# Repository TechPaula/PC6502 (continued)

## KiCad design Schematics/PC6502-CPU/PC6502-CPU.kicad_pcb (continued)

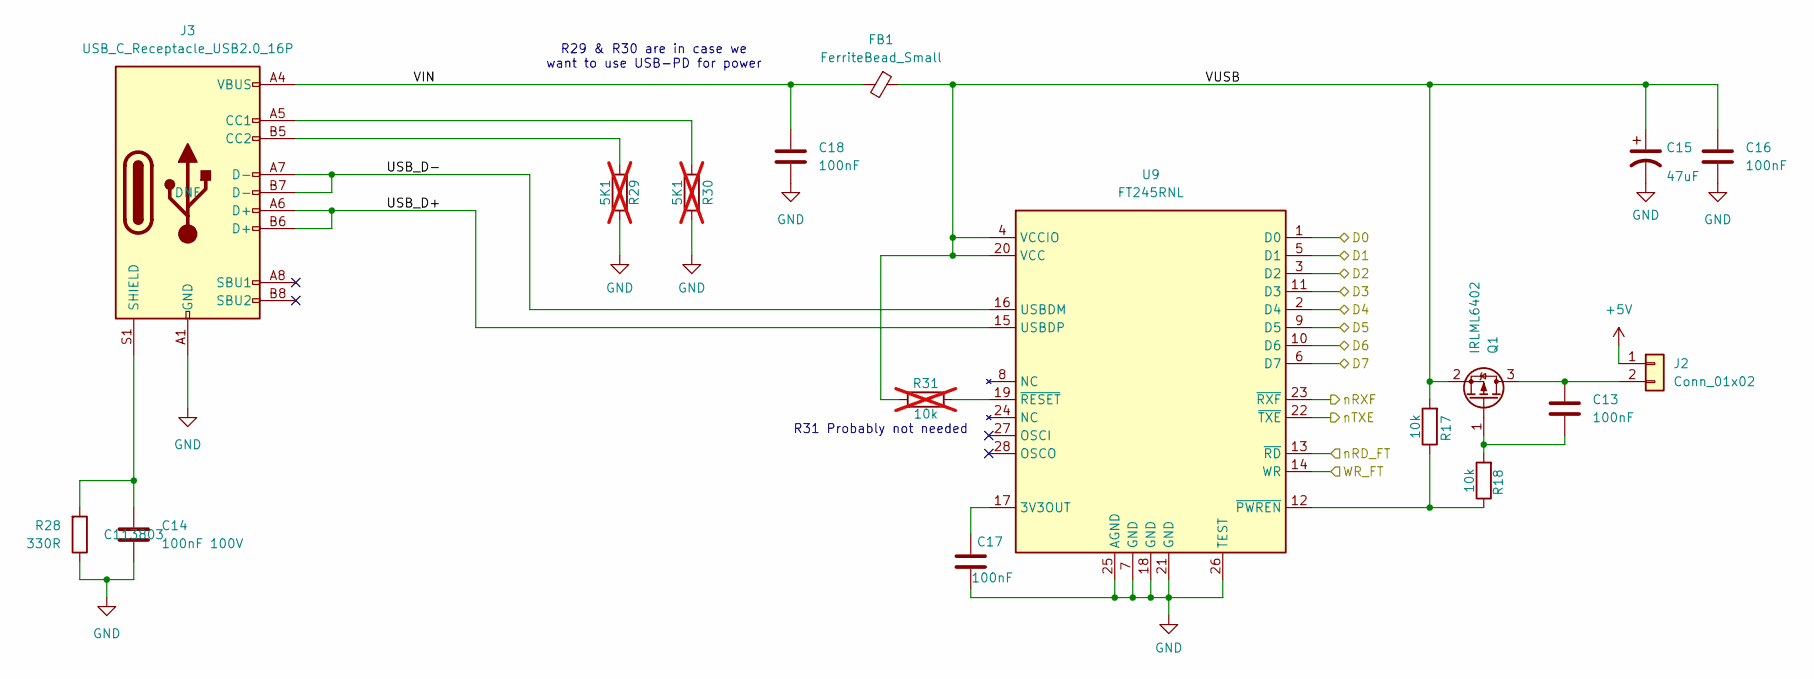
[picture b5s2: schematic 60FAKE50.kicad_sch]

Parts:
C13, C17: 100nF; C_0603_1608Metric_Pad1.08x0.95mm_HandSolder; LCSC C113803
C14: 100nF 100V; C_0603_1608Metric; LCSC C113803
C15: 47uF; C_1206_3216Metric; LCSC C96123
C16, C18: 100nF; C_0805_2012Metric; LCSC C49678
FB1: FerriteBead_Small; L_0805_2012Metric_Pad1.05x1.20mm_HandSolder; LCSC DNF
J2: Conn_01x02; PinHeader_1x02_P2.54mm_Horizontal; LCSC DNF
J3: USB_C_Receptacle_USB2.0_16P; USB_C_Receptacle_HCTL_HC-TYPE-C-16P-01A; LCSC DNF
Q1: IRLML6402; SOT-23; LCSC C2593
R17, R18: 10k; R_0603_1608Metric_Pad0.98x0.95mm_HandSolder; LCSC C25744
R28: 330R; R_0402_1005Metric; LCSC C25104
R29, R30: 5K1; R_0603_1608Metric_Pad0.98x0.95mm_HandSolder; LCSC DNF; not fitted
R31: 10k; R_0603_1608Metric_Pad0.98x0.95mm_HandSolder; LCSC DNF; not fitted
U9: FT245RNL; SSOP-28_5.3x10.2mm_P0.65mm; LCSC C6558294

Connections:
+5V: J2.1; also elsewhere on the board
/60FAKE50/USB_D+: J3.A6 (D+), J3.B6 (D+), U9.15 (USBDP)
/60FAKE50/USB_D-: J3.A7 (D-), J3.B7 (D-), U9.16 (USBDM)
/60FAKE50/VIN: C18.1, FB1.2, J3.A4 (VBUS), J3.A9 (VBUS), J3.B4 (VBUS), J3.B9 (VBUS)
/60FAKE50/VUSB: C15.1, C16.1, FB1.1, Q1.2 (S), R17.2, R31.2, U9.4 (VCCIO), U9.20 (VCC)
/D0: U9.1 (D0); also elsewhere on the board
/D1: U9.5 (D1); also elsewhere on the board
/D2: U9.3 (D2); also elsewhere on the board
/D3: U9.11 (D3); also elsewhere on the board
/D4: U9.2 (D4); also elsewhere on the board
/D5: U9.9 (D5); also elsewhere on the board
/D6: U9.10 (D6); also elsewhere on the board
/D7: U9.6 (D7); also elsewhere on the board
GND: C14.2, C15.2, C16.2, C17.2, C18.2, J3.A1 (GND), J3.A12 (GND), J3.B1 (GND), J3.B12 (GND), R28.1, R29.1, R30.1, U9.7 (GND), U9.18 (GND), U9.21 (GND), U9.25 (AGND), U9.26 (TEST); also elsewhere on the board
unnamed: C13.1, J2.2, Q1.3 (D)
unnamed: J3.A5 (CC1), R30.2
unnamed: J3.B5 (CC2), R29.2
unnamed: C14.1, J3.S1 (SHIELD), R28.2
unnamed: C13.2, Q1.1 (G), R18.2
unnamed: C17.1, U9.17 (3V3OUT)
unnamed: R17.1, R18.1, U9.12 (~PWREN)
unnamed: R31.1, U9.19 (~RESET)
WR_FT: U9.14 (WR); also elsewhere on the board
nRD_FT: U9.13 (~RD); also elsewhere on the board
nRXF: U9.23 (~RXF); also elsewhere on the board
nTXE: U9.22 (~TXE); also elsewhere on the board

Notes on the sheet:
R29 & R30 are in case we want to use USB-PD for power
R31 Probably not needed

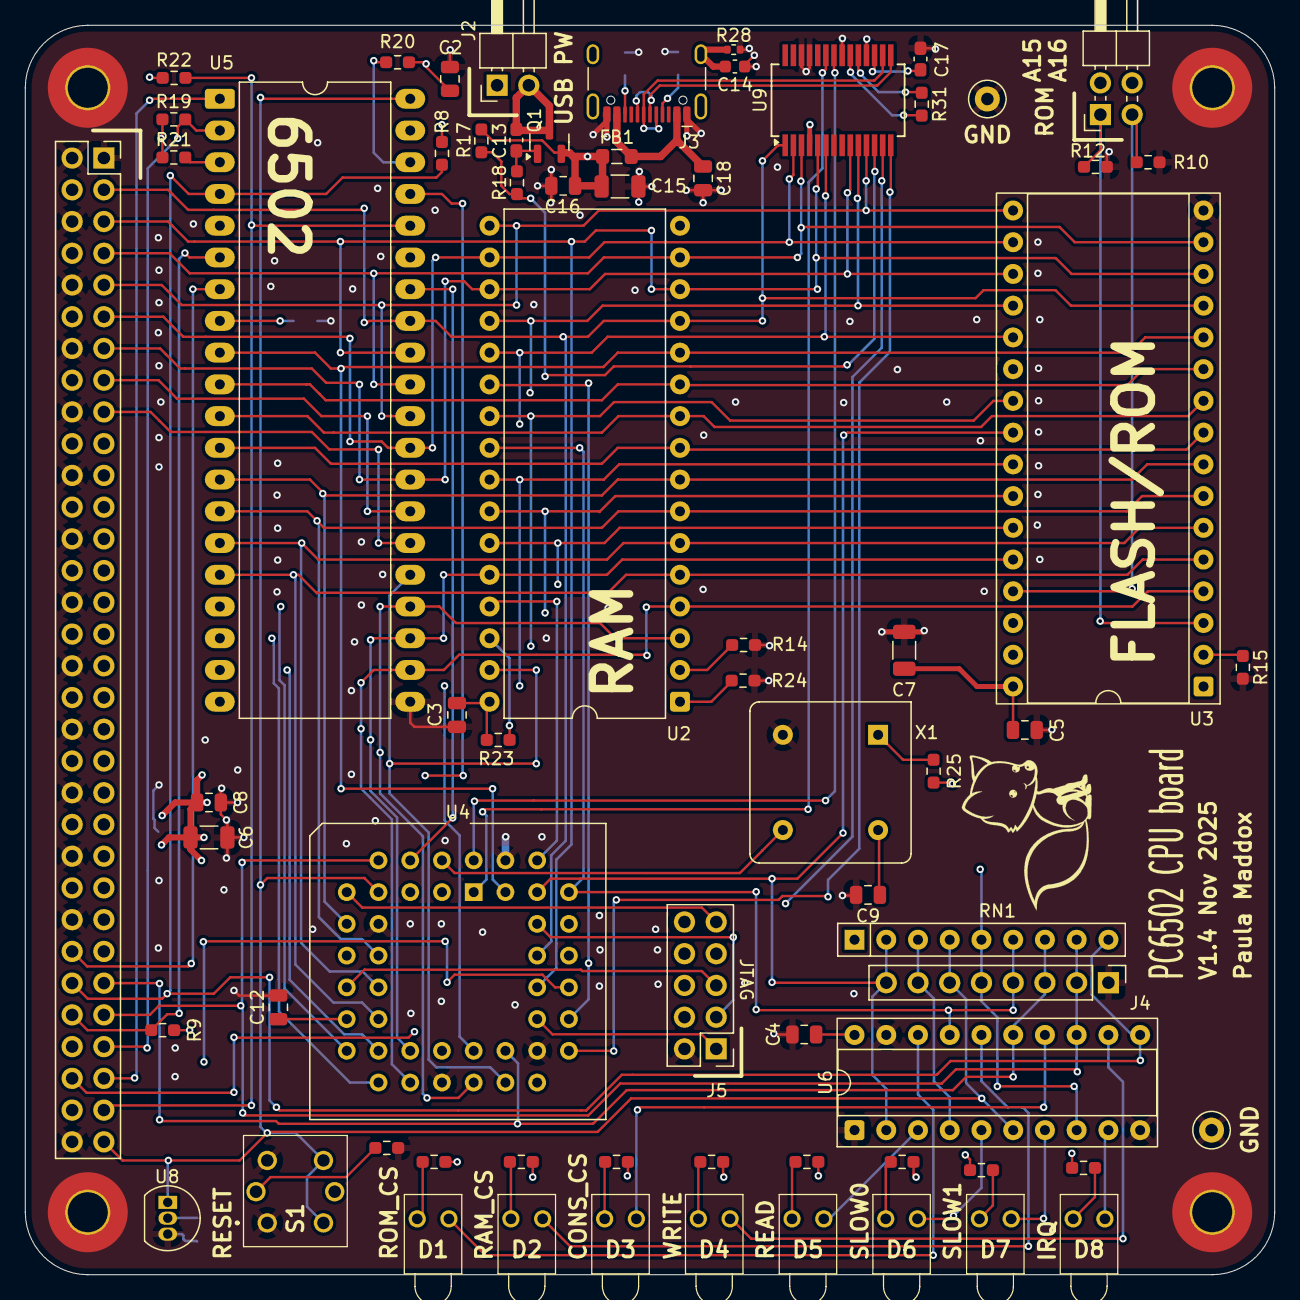
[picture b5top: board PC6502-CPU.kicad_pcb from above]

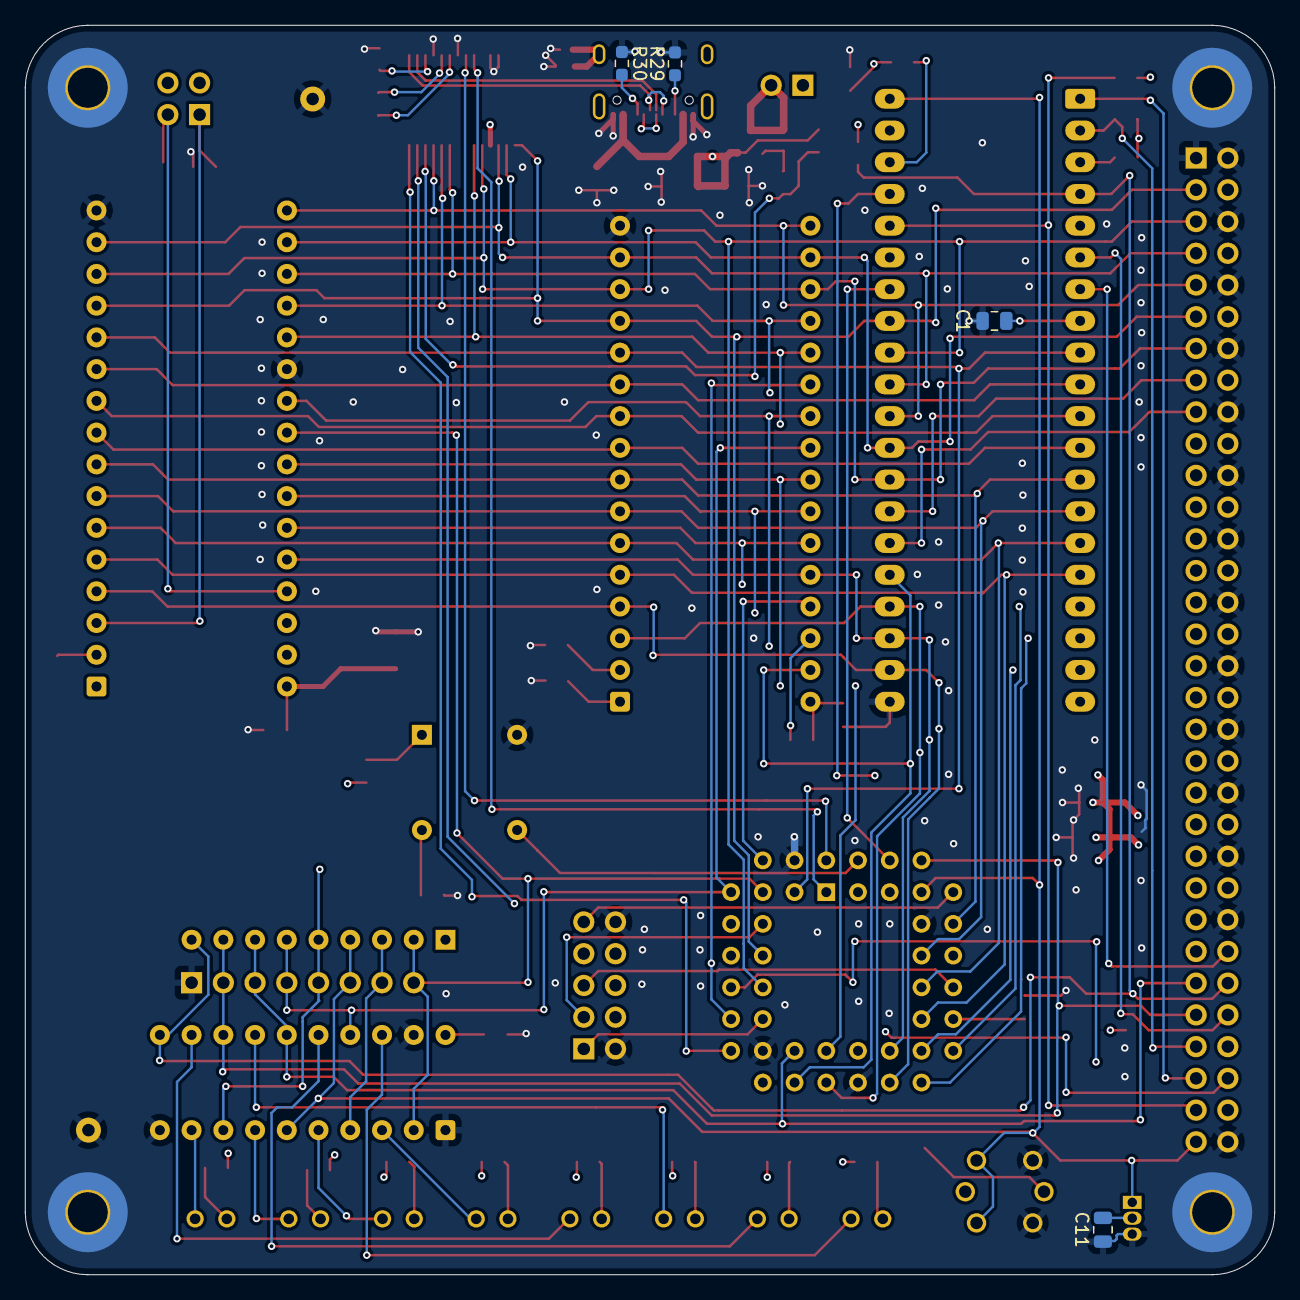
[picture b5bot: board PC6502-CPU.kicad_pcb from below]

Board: 4 copper layers, 100.0 x 100.0 mm, 78 parts (4 on the bottom side), 89 nets.

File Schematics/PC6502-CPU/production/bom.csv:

Designator,Footprint,Quantity,Value,LCSC Part #
"C1, C11, C12, C16, C18, C2, C3, C4, C5, C8, C9",0805,11,100nF,C49678
"C13, C17",0603,2,100nF,C113803
C14,0603,1,100nF 100V,C113803
"C15, C6, C7",1206,3,47uF,C96123
"D1, D2, D3, D4, D5, D6, D7, D8",LTL4221NHBP,8,LED,DNF
FB1,0805,1,FerriteBead_Small,DNF
J1,PinSocket_2x32_P2.54mm_Vertical,1,BUS,DNF
J2,PinHeader_1x02_P2.54mm_Horizontal,1,Conn_01x02,DNF
J3,USB_C_Receptacle_HCTL_HC-TYPE-C-16P-01A,1,USB_C_Receptacle_USB2.0_16P,DNF
J4,PinHeader_1x08_P2.54mm_Vertical,1,TEST,DNF
J5,PinHeader_2x05_P2.54mm_Vertical,1,Conn_02x05_Odd_Even,DNF
J6,PinHeader_2x02_P2.54mm_Horizontal,1,Conn_02x02_Odd_Even,D NF
Q1,SOT-23,1,IRLML6402,C2593
"R1, R11, R16, R2, R3, R4, R5, R6, R7",0603,9,470R,C23179
"R10, R12, R14, R15, R17, R18, R23, R24",0603,8,10K,C25744
"R19, R20, R22, R25, R8, R9",0603,6,3K3,C25890
R21,0603,1,3K3,DNF
R28,0402,1,330R,C25104
"R29, R30",0603,2,5K1,DNF
R31,0603,1,10k,DNF
RN1,R_Array_SIP9,1,10K,DNF
S1,TL1250F180RQRCLR,1,TL1250F180RQRCLR,DNF
"TP5, TP6",TestPoint_Loop_D1.80mm_Drill1.0mm_Beaded,2,TestPoint,DNF
U2,DIP-32_W15.24mm,1,AS6C4008-55PCN,DNF
U3,DIP-32_W15.24mm_Socket,1,SST39SF010,DNF
U4,PLCC-44_THT-Socket,1,ATF1504AS,DNF
U5,DIP-40_W15.24mm_LongPads,1,W65C02,DNF
U6,DIP-20_W7.62mm_Socket,1,74AHC244,DNF
U8,TO-92_Inline,1,MCP130-450DI/TO,DNF
U9,SSOP-28_5.3x10.2mm_P0.65mm,1,FT245RNL,C6558294
X1,Oscillator_DIP-8,1,CXO_DIP8,DNF

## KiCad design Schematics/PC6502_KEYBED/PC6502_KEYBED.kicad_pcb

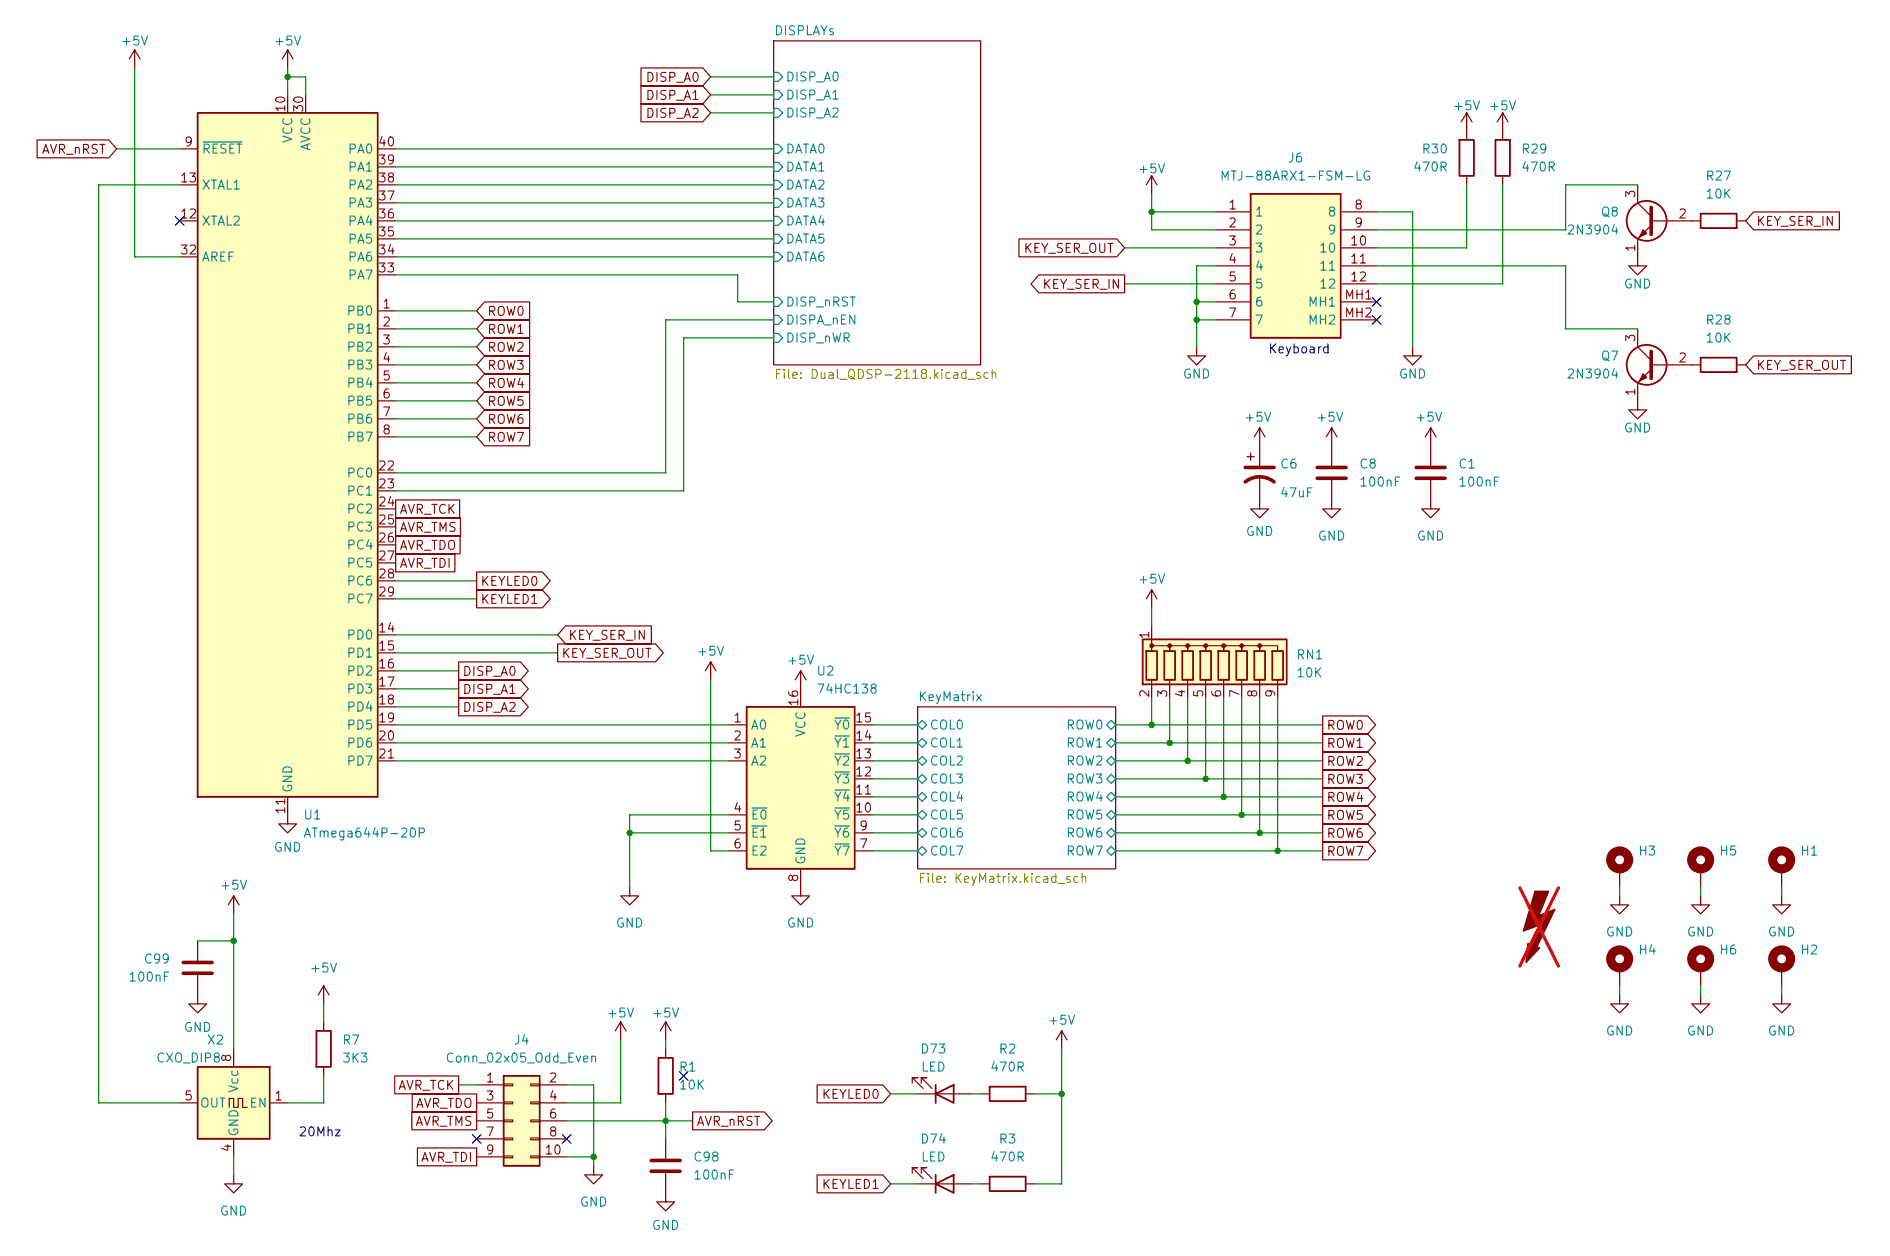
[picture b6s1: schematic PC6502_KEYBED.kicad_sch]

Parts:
C1, C8, C98, C99: 100nF; C_0805_2012Metric; LCSC C49678
C6: 47uF; C_1206_3216Metric; LCSC C96123
D73, D74: LED; LED_D5.0mm; LCSC DNF
FOX1: SYM_Flash_Large; Fox_avatar_18mm; LCSC DNF; not fitted
H1, H2, H3, H4, H5, H6: MountingHole_Pad; MountingHole_3.2mm_M3_Pad_TopBottom; LCSC DNF
J4: Conn_02x05_Odd_Even; PinHeader_2x05_P2.54mm_Vertical; LCSC DNF
J6: MTJ-88ARX1-FSM-LG; MTJ88ARX1FSMLG; Mouser Part Number 737-MTJ88ARX1FSMLG
Q7, Q8: 2N3904; TO-92_Inline; LCSC DNF
R1, R27, R28: 10K; R_0603_1608Metric_Pad0.98x0.95mm_HandSolder; LCSC DNF
R2, R3, R29, R30: 470R; R_0603_1608Metric_Pad0.98x0.95mm_HandSolder; LCSC DNF
R7: 3K3; R_0603_1608Metric_Pad0.98x0.95mm_HandSolder; LCSC DNF
RN1: 10K; R_Array_SIP9; LCSC DNF
U1: ATmega644P-20P; DIP-40_W15.24mm; LCSC DNF
U2: 74HC138
X2: CXO_DIP8; Oscillator_DIP-8; LCSC DNF

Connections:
+5V: C1.1, C6.1, C8.1, C99.1, J4.4, J6.1, J6.2, R1.1, R2.1, R3.1, R7.1, R29.2, R30.2, RN1.1 (common), U1.10 (VCC), U1.30 (AVCC), U1.32 (AREF), U2.6 (E2), U2.16 (VCC), X2.8 (Vcc); also elsewhere on the board
/DISPLAYs/DATA0: U1.40 (PA0); also elsewhere on the board
/DISPLAYs/DATA1: U1.39 (PA1); also elsewhere on the board
/DISPLAYs/DATA2: U1.38 (PA2); also elsewhere on the board
/DISPLAYs/DATA3: U1.37 (PA3); also elsewhere on the board
/DISPLAYs/DATA4: U1.36 (PA4); also elsewhere on the board
/DISPLAYs/DATA5: U1.35 (PA5); also elsewhere on the board
/DISPLAYs/DATA6: U1.34 (PA6); also elsewhere on the board
/DISPLAYs/DISPA_nEN: U1.22 (PC0); also elsewhere on the board
/DISPLAYs/DISP_nRST: U1.33 (PA7); also elsewhere on the board
/DISPLAYs/DISP_nWR: U1.23 (PC1); also elsewhere on the board
/KeyMatrix/COL0: U2.15 (~Y0); also elsewhere on the board
/KeyMatrix/COL1: U2.14 (~Y1); also elsewhere on the board
/KeyMatrix/COL2: U2.13 (~Y2); also elsewhere on the board
/KeyMatrix/COL3: U2.12 (~Y3); also elsewhere on the board
/KeyMatrix/COL4: U2.11 (~Y4); also elsewhere on the board
/KeyMatrix/COL5: U2.10 (~Y5); also elsewhere on the board
/KeyMatrix/COL6: U2.9 (~Y6); also elsewhere on the board
/KeyMatrix/COL7: U2.7 (~Y7); also elsewhere on the board
AVR_TCK: J4.1, U1.24 (PC2)
AVR_TDI: J4.9, U1.27 (PC5)
AVR_TDO: J4.3, U1.26 (PC4)
AVR_TMS: J4.5, U1.25 (PC3)
AVR_nRST: C98.1, J4.6, R1.2, U1.9 (~RESET)
DISP_A0: U1.16 (PD2); also elsewhere on the board
DISP_A1: U1.17 (PD3); also elsewhere on the board
DISP_A2: U1.18 (PD4); also elsewhere on the board
GND: C1.2, C6.2, C8.2, C98.2, C99.2, H1.1, H2.1, H3.1, H4.1, H5.1, H6.1, J4.2, J4.10, J6.4, J6.6, J6.7, J6.8, Q7.1 (E), Q8.1 (E), U1.11 (GND), U1.31 (GND), U2.4 (~E0), U2.5 (~E1), U2.8 (GND), X2.4 (GND); also elsewhere on the board
KEYLED0: D73.1 (K), U1.28 (PC6)
KEYLED1: D74.1 (K), U1.29 (PC7)
KEY_SER_IN: J6.5, R27.2, U1.14 (PD0)
KEY_SER_OUT: J6.3, R28.2, U1.15 (PD1)
unnamed: D73.2 (A), R2.2
unnamed: D74.2 (A), R3.2
unnamed: J6.10, R30.1
unnamed: J6.12, R29.1
unnamed: Q7.2 (B), R28.1
unnamed: J6.11, Q7.3 (C)
unnamed: Q8.2 (B), R27.1
unnamed: J6.9, Q8.3 (C)
unnamed: U1.19 (PD5), U2.1 (A0)
unnamed: U1.20 (PD6), U2.2 (A1)
unnamed: U1.21 (PD7), U2.3 (A2)
unnamed: U1.13 (XTAL1), X2.5 (OUT)
unnamed: R7.2, X2.1 (EN)
ROW0: RN1.2 (R1), U1.1 (PB0); also elsewhere on the board
ROW1: RN1.3 (R2), U1.2 (PB1); also elsewhere on the board
ROW2: RN1.4 (R3), U1.3 (PB2); also elsewhere on the board
ROW3: RN1.5 (R4), U1.4 (PB3); also elsewhere on the board
ROW4: RN1.6 (R5), U1.5 (PB4); also elsewhere on the board
ROW5: RN1.7 (R6), U1.6 (PB5); also elsewhere on the board
ROW6: RN1.8 (R7), U1.7 (PB6); also elsewhere on the board
ROW7: RN1.9 (R8), U1.8 (PB7); also elsewhere on the board

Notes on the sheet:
20Mhz
Keyboard

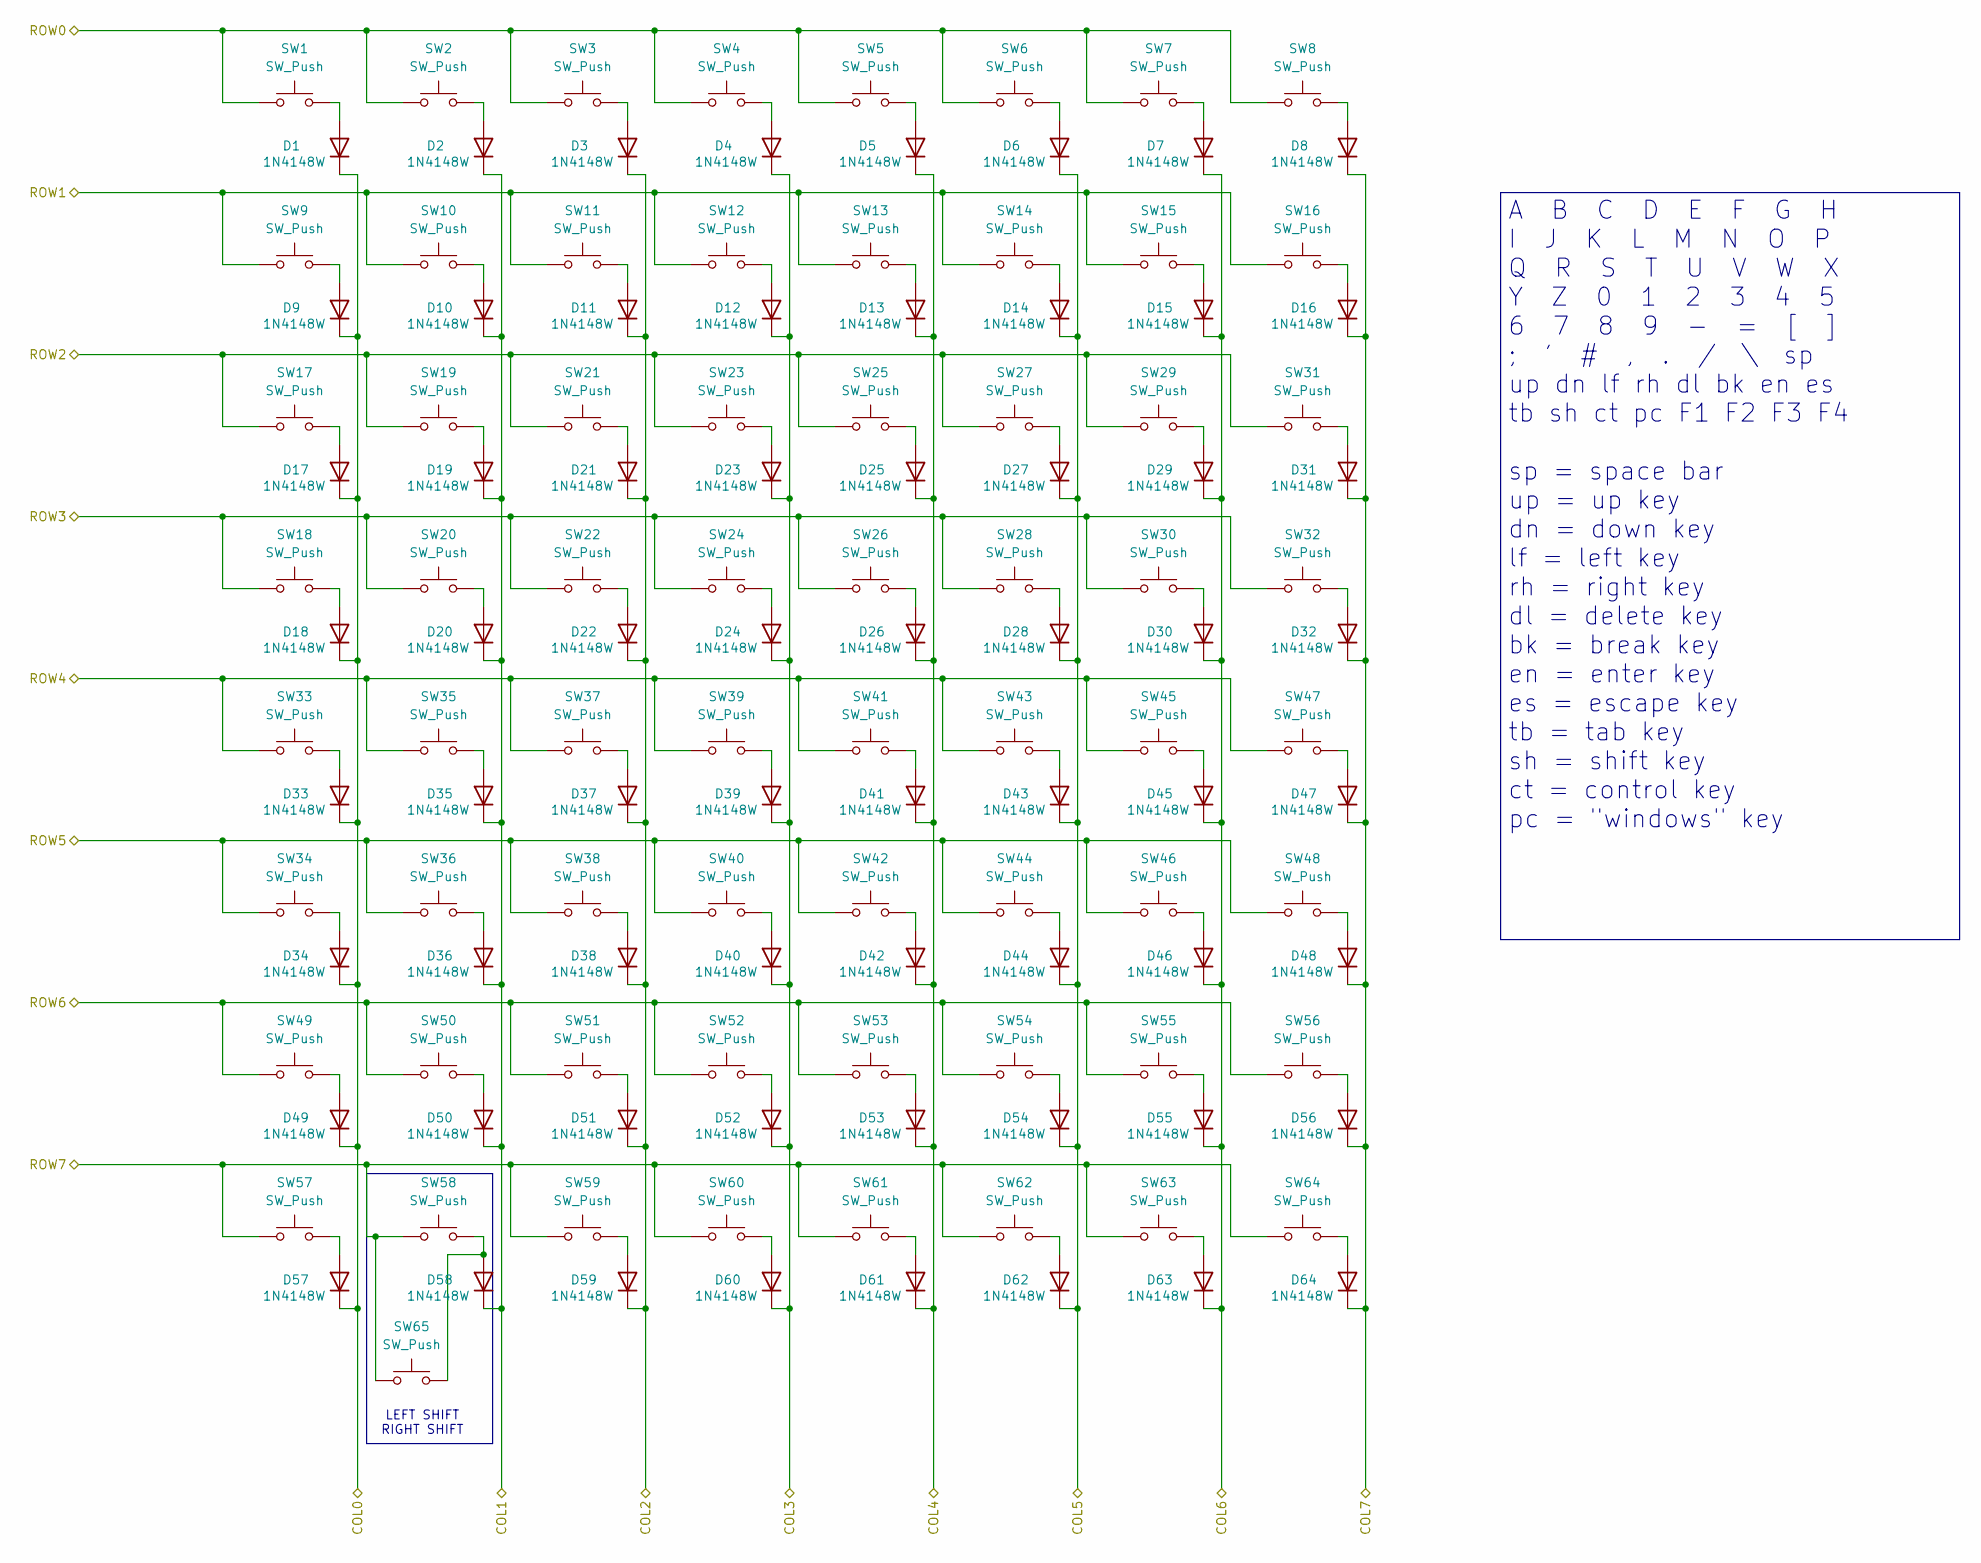
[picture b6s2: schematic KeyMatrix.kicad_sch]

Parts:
D1, D2, D3, D4, D5, D6, D7, D8, D9, D10, D11, D12, D13, D14, D15, D16, D17, D18, D19, D20, D21, D22, D23, D24, D25, D26, D27, D28, D29, D30, D31, D32, D33, D34, D35, D36, D37, D38, D39, D40, D41, D42, D43, D44, D45, D46, D47, D48, D49, D50, D51, D52, D53, D54, D55, D56, D57, D58, D59, D60, D61, D62, D63, D64: 1N4148W; D_SOD-123; LCSC C2099
SW1, SW2, SW3, SW4, SW5, SW6, SW7, SW8, SW9, SW10, SW11, SW12, SW13, SW14, SW15, SW16, SW17, SW18, SW19, SW20, SW21, SW22, SW23, SW24, SW25, SW26, SW27, SW28, SW29, SW30, SW31, SW32, SW33, SW34, SW35, SW36, SW37, SW38, SW39, SW40, SW41, SW42, SW43, SW44, SW45, SW46, SW47, SW48, SW49, SW50, SW51, SW52, SW53, SW54, SW55, SW56, SW57, SW58, SW59, SW60, SW61, SW62, SW63, SW64, SW65: SW_Push; SW_Cherry_MX_1.00u_PCB_LED; LCSC DNF

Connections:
/KeyMatrix/COL0: D1.1 (K), D9.1 (K), D17.1 (K), D18.1 (K), D33.1 (K), D34.1 (K), D49.1 (K), D57.1 (K); also elsewhere on the board
/KeyMatrix/COL1: D2.1 (K), D10.1 (K), D19.1 (K), D20.1 (K), D35.1 (K), D36.1 (K), D50.1 (K), D58.1 (K); also elsewhere on the board
/KeyMatrix/COL2: D3.1 (K), D11.1 (K), D21.1 (K), D22.1 (K), D37.1 (K), D38.1 (K), D51.1 (K), D59.1 (K); also elsewhere on the board
/KeyMatrix/COL3: D4.1 (K), D12.1 (K), D23.1 (K), D24.1 (K), D39.1 (K), D40.1 (K), D52.1 (K), D60.1 (K); also elsewhere on the board
/KeyMatrix/COL4: D5.1 (K), D13.1 (K), D25.1 (K), D26.1 (K), D41.1 (K), D42.1 (K), D53.1 (K), D61.1 (K); also elsewhere on the board
/KeyMatrix/COL5: D6.1 (K), D14.1 (K), D27.1 (K), D28.1 (K), D43.1 (K), D44.1 (K), D54.1 (K), D62.1 (K); also elsewhere on the board
/KeyMatrix/COL6: D7.1 (K), D15.1 (K), D29.1 (K), D30.1 (K), D45.1 (K), D46.1 (K), D55.1 (K), D63.1 (K); also elsewhere on the board
/KeyMatrix/COL7: D8.1 (K), D16.1 (K), D31.1 (K), D32.1 (K), D47.1 (K), D48.1 (K), D56.1 (K), D64.1 (K); also elsewhere on the board
unnamed: D1.2 (A), SW1.2
unnamed: D2.2 (A), SW2.2
unnamed: D3.2 (A), SW3.2
unnamed: D4.2 (A), SW4.2
unnamed: D5.2 (A), SW5.2
unnamed: D6.2 (A), SW6.2
unnamed: D7.2 (A), SW7.2
unnamed: D8.2 (A), SW8.2
unnamed: D9.2 (A), SW9.2
unnamed: D10.2 (A), SW10.2
unnamed: D11.2 (A), SW11.2
unnamed: D12.2 (A), SW12.2
unnamed: D13.2 (A), SW13.2
unnamed: D14.2 (A), SW14.2
unnamed: D15.2 (A), SW15.2
unnamed: D16.2 (A), SW16.2
unnamed: D17.2 (A), SW17.2
unnamed: D18.2 (A), SW18.2
unnamed: D19.2 (A), SW19.2
unnamed: D20.2 (A), SW20.2
unnamed: D21.2 (A), SW21.2
unnamed: D22.2 (A), SW22.2
unnamed: D23.2 (A), SW23.2
unnamed: D24.2 (A), SW24.2
unnamed: D25.2 (A), SW25.2
unnamed: D26.2 (A), SW26.2
unnamed: D27.2 (A), SW27.2
unnamed: D28.2 (A), SW28.2
unnamed: D29.2 (A), SW29.2
unnamed: D30.2 (A), SW30.2
unnamed: D31.2 (A), SW31.2
unnamed: D32.2 (A), SW32.2
unnamed: D33.2 (A), SW33.2
unnamed: D34.2 (A), SW34.2
unnamed: D35.2 (A), SW35.2
unnamed: D36.2 (A), SW36.2
unnamed: D37.2 (A), SW37.2
unnamed: D38.2 (A), SW38.2
unnamed: D39.2 (A), SW39.2
unnamed: D40.2 (A), SW40.2
unnamed: D41.2 (A), SW41.2
unnamed: D42.2 (A), SW42.2
unnamed: D43.2 (A), SW43.2
unnamed: D44.2 (A), SW44.2
unnamed: D45.2 (A), SW45.2
unnamed: D46.2 (A), SW46.2
unnamed: D47.2 (A), SW47.2
unnamed: D48.2 (A), SW48.2
unnamed: D49.2 (A), SW49.2
unnamed: D50.2 (A), SW50.2
unnamed: D51.2 (A), SW51.2
unnamed: D52.2 (A), SW52.2
unnamed: D53.2 (A), SW53.2
unnamed: D54.2 (A), SW54.2
unnamed: D55.2 (A), SW55.2
unnamed: D56.2 (A), SW56.2
unnamed: D57.2 (A), SW57.2
unnamed: D58.2 (A), SW58.2, SW65.2
unnamed: D59.2 (A), SW59.2
unnamed: D60.2 (A), SW60.2
unnamed: D61.2 (A), SW61.2
unnamed: D62.2 (A), SW62.2
unnamed: D63.2 (A), SW63.2
unnamed: D64.2 (A), SW64.2
ROW0: SW1.1, SW2.1, SW3.1, SW4.1, SW5.1, SW6.1, SW7.1, SW8.1; also elsewhere on the board
ROW1: SW9.1, SW10.1, SW11.1, SW12.1, SW13.1, SW14.1, SW15.1, SW16.1; also elsewhere on the board
ROW2: SW17.1, SW19.1, SW21.1, SW23.1, SW25.1, SW27.1, SW29.1, SW31.1; also elsewhere on the board
ROW3: SW18.1, SW20.1, SW22.1, SW24.1, SW26.1, SW28.1, SW30.1, SW32.1; also elsewhere on the board
ROW4: SW33.1, SW35.1, SW37.1, SW39.1, SW41.1, SW43.1, SW45.1, SW47.1; also elsewhere on the board
ROW5: SW34.1, SW36.1, SW38.1, SW40.1, SW42.1, SW44.1, SW46.1, SW48.1; also elsewhere on the board
ROW6: SW49.1, SW50.1, SW51.1, SW52.1, SW53.1, SW54.1, SW55.1, SW56.1; also elsewhere on the board
ROW7: SW57.1, SW58.1, SW59.1, SW60.1, SW61.1, SW62.1, SW63.1, SW64.1, SW65.1; also elsewhere on the board

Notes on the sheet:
LEFT SHIFT RIGHT SHIFT
A B C D E F G H I J K L M N O P Q R S T U V W X Y Z 0 1 2 3 4 5 6 7 8 9 - = [ ] ; ' # , . / \ sp up dn lf rh dl bk en es tb sh ct pc F1 F2 F3 F4 sp = space bar up = up key dn = down key lf = left key rh = right key dl = delete key bk = break key en = enter key es = escape key tb = tab key sh = shif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

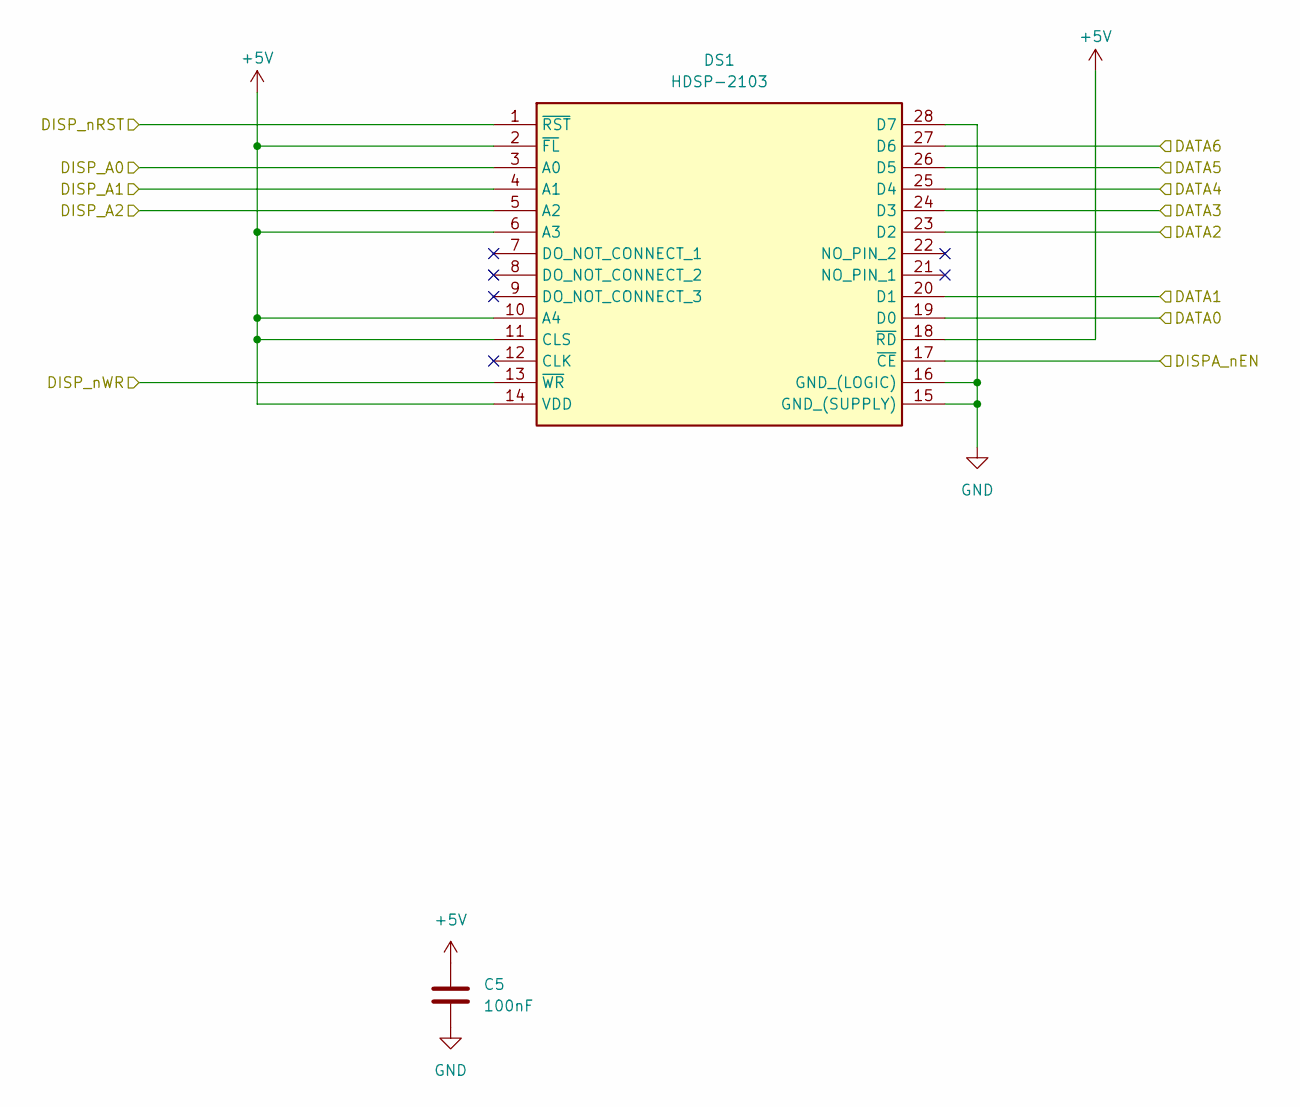
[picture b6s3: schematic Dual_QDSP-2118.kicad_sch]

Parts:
C5: 100nF; C_0805_2012Metric; LCSC C49678
DS1: HDSP-2103; DIPS1524W64P254L7087H685Q28N; Manufacturer_Part_Number HDSP-2503; Mouser Part Number 630-HDSP-2503

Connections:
+5V: C5.1, DS1.2 (~FL), DS1.6 (A3), DS1.10 (A4), DS1.11 (CLS), DS1.14 (VDD), DS1.18 (~RD); also elsewhere on the board
/DISPLAYs/DATA0: DS1.19 (D0); also elsewhere on the board
/DISPLAYs/DATA1: DS1.20 (D1); also elsewhere on the board
/DISPLAYs/DATA2: DS1.23 (D2); also elsewhere on the board
/DISPLAYs/DATA3: DS1.24 (D3); also elsewhere on the board
/DISPLAYs/DATA4: DS1.25 (D4); also elsewhere on the board
/DISPLAYs/DATA5: DS1.26 (D5); also elsewhere on the board
/DISPLAYs/DATA6: DS1.27 (D6); also elsewhere on the board
/DISPLAYs/DISPA_nEN: DS1.17 (~CE); also elsewhere on the board
/DISPLAYs/DISP_nRST: DS1.1 (~RST); also elsewhere on the board
/DISPLAYs/DISP_nWR: DS1.13 (~WR); also elsewhere on the board
DISP_A0: DS1.3 (A0); also elsewhere on the board
DISP_A1: DS1.4 (A1); also elsewhere on the board
DISP_A2: DS1.5 (A2); also elsewhere on the board
GND: C5.2, DS1.15 (GND_(SUPPLY)), DS1.16 (GND_(LOGIC)), DS1.28 (D7); also elsewhere on the board

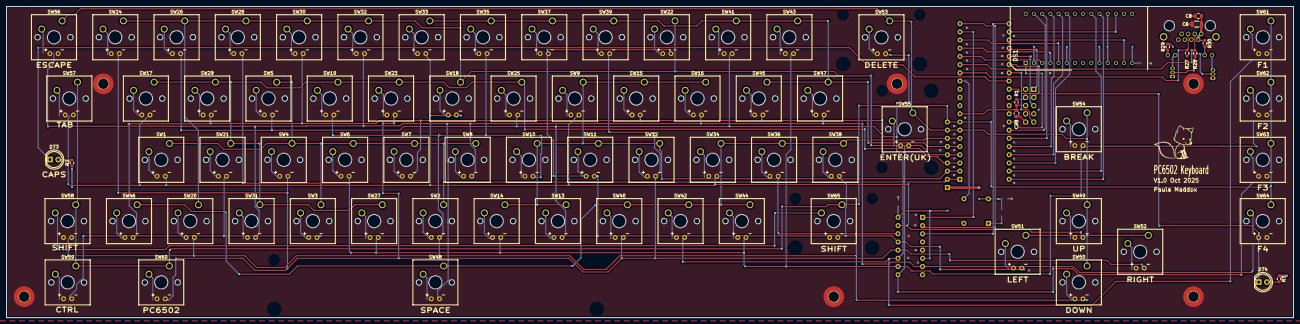
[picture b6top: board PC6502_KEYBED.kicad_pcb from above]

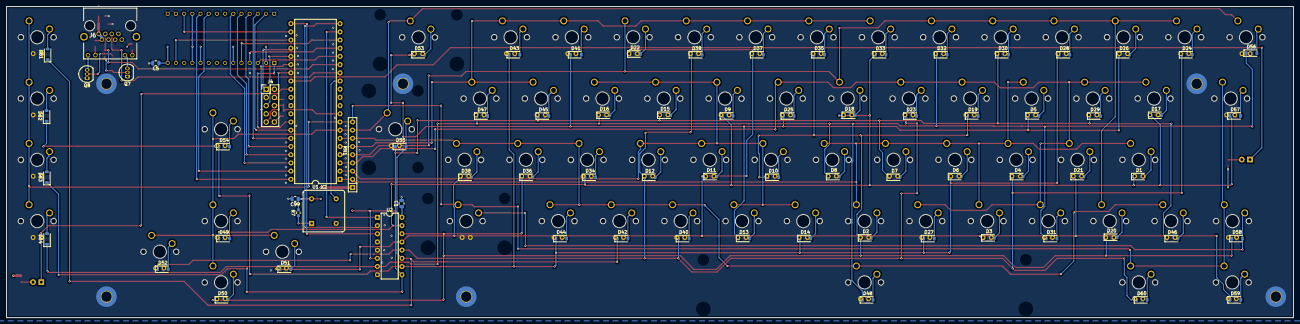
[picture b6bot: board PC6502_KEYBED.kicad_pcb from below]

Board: 4 copper layers, 399.0 x 96.4 mm, 161 parts (76 on the bottom side), 117 nets.

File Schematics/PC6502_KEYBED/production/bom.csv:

Designator,Footprint,Quantity,Value,LCSC Part #
"C1, C5, C8, C98, C99",0805,5,100nF,C49678
C6,1206,1,47uF,C96123
"D1, D10, D11, D12, D13, D14, D15, D16, D17, D18, D19, D2, D20, D21, D22, D23, D24, D25, D26, D27, D28, D29, D3, D30, D31, D32, D33, D34, D35, D36, D37, D38, D39, D4, D40, D41, D42, D43, D44, D45, D46, D47, D48, D49, D5, D50, D51, D52, D53, D54, D55, D56, D57, D58, D59, D6, D60, D61, D62, D63, D64, D7, D8, D9",D_SOD-123,64,1N4148W,C2099
"D73, D74",LED_D5.0mm,2,LED,DNF
DS1,DIPS1524W64P254L7087H685Q28N,1,HDSP-2503,DNF
"H1, H2, H3, H4, H5, H6",MountingHole_3.2mm_M3_Pad_TopBottom,6,MountingHole_Pad,DNF
J4,PinHeader_2x05_P2.54mm_Vertical,1,Conn_02x05_Odd_Even,DNF
J6,MTJ88ARX1FSMLG,1,MTJ-88ARX1-FSM-LG,DNF
"Q7, Q8",TO-92_Inline,2,2N3904,DNF
"R1, R27, R28",0603,3,10K,DNF
"R2, R29, R3, R30",0603,4,470R,DNF
R7,0603,1,3K3,DNF
RN1,R_Array_SIP9,1,10K,DNF
"SW1, SW10, SW11, SW12, SW13, SW14, SW15, SW16, SW17, SW18, SW19, SW2, SW20, SW21, SW22, SW23, SW24, SW25, SW26, SW27, SW28, SW29, SW3, SW30, SW31, SW32, SW33, SW34, SW35, SW36, SW37, SW38, SW39, SW4, SW40, SW41, SW42, SW43, SW44, SW45, SW46, SW47, SW49, SW5, SW50, SW51, SW52, SW54, SW56, SW58, SW59, SW6, SW60, SW61, SW62, SW63, SW64, SW7, SW8, SW9",SW_Cherry_MX_1.00u_PCB,60,SW_Push,DNF
SW48,SW_Cherry_MX_6.25u_PCB,1,SW_Push,DNF
"SW53, SW65",SW_Cherry_MX_2.00u_PCB,2,SW_Push,DNF
SW55,SW_Cherry_MX_ISOEnter_PCB,1,SW_Push,DNF
SW57,SW_Cherry_MX_1.50u_PCB,1,SW_Push,DNF
U1,DIP-40_W15.24mm,1,ATmega644P-20P,DNF
U2,DIP-16_W7.62mm,1,74HC238,DNF
X2,Oscillator_DIP-8,1,CXO_DIP8,DNF
